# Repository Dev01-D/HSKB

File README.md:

# HSKB – Happy Sabi KeyBoard

## About the HSKB

The HSKB is a custom mechanical keyboard inspired by the minimalist layout and functionality of the HHKB (Happy Hacking Keyboard). It reflects a philosophy of simplicity, precision, and personal expression.

Designed with a true HHKB layout, the HSKB features a 6u spacebar and an integrated plate design that supports both plate-mounted and PCB-mounted stabilizers. Drawing inspiration from the legendary HHKB and driven by a passion for thoughtful design and community collaboration, this project has been a personal journey—learning new software, iterating through multiple prototypes, and spending approximately three months refining every detail.

I am excited to share the HSKB with the open-source community and hope it inspires others to create and contribute. This project would not have been possible without the support and inspiration from the keyboard community.

## Why Choose the HSKB?

Many keyboards with a similar HHKB-inspired layout are often positioned as luxury items, carrying a high price tag and limited customization options. The HSKB offers a more affordable entry point without sacrificing quality or flexibility. Its open-source nature means you can modify and adapt it to suit your preferences—whether it's changing the key mapping, adjusting the stabilizers, or customizing the case.

The HSKB provides a unique balance of cost-efficiency and personalization. It's an excellent option for enthusiasts looking to explore the HHKB layout without breaking the bank. Whether you're new to mechanical keyboards or an experienced hobbyist, the HSKB offers a rewarding, hands-on experience while remaining accessible and adaptable.

## Unity Switch & Andy's Man Club

This project is also inspired by **Matty's Unity switch**, created in support of **Andy's Man Club**, a mental health charity promoting open conversations and community support. As part of this commitment, one of the five initial HSKBs will be donated to a charity raffle to raise funds for this meaningful cause.

If you use or modify this project, please consider supporting **Andy's Man Club** or a mental health charity in your community.

- https://andysmanclub.co.uk/
- https://thoccexchange.com/

## Features

- **Minimalist Layout** – Inspired by the HHKB design
- **Custom PCB & Case Files** – Fully customizable and open-source (thanks to **TheVoid** for helping with this)
- **Community-Driven** – Built with love, feedback, and support

## What's Included

- [PCB design files (KiCad)](https://github.com/Dev01-D/HSKB/tree/main/PCB%20Files)
- [Case design files (STEP, STL for 3D printing)](https://github.com/Dev01-D/HSKB/tree/main/HSKB%20STL)
- [HS Firmware configuration (QMK/VIA-compatible)](https://github.com/Dev01-D/HSKB/tree/main/PCB%20Files/VoidHHKB-Hotswap/firmware)
- [Solder Firmware configuration (QMK/VIA-compatible)](https://github.com/Dev01-D/HSKB/tree/main/PCB%20Files/VoidHHKB-Solder/firmware)

## Getting Started

1. **Clone the repository:**
    ```bash
    git clone https://github.com/Dev01-D/hskb.git
    cd hskb
    ```

2. **Explore the design files:**
   - PCB files: Located in the `/pcb` directory
   - Case files: Located in the `/case` directory
   - Firmware: Instructions in `/firmware` for flashing QMK/VIA

3. **Manufacture & Build:**
   - Order your PCB from your preferred manufacturer
   - Print the case using the provided STL files
   - Assemble the board using the included BOM (Bill of Materials)

## Contributing

Contributions and improvements are welcome! Feel free to submit issues, pull requests, or ideas to enhance the HSKB.

1. Fork the repository
2. Create a new branch
3. Submit a pull request

## License

This project is released under the **MIT License** – you're free to use, modify, and share it. Please credit this repository if you share your own builds.

## Support

If you build your own HSKB, I would love to see it! Share your creations and thoughts.

Consider donating to **Andy's Man Club** or any mental health charity to help continue supporting important community work.

Thank you for being a part of the journey.

**Happy building!**

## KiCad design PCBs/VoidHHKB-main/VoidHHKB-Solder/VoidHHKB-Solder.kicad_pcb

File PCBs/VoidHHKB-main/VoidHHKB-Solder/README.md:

# VoidHHKB-Solder

## Ordering from JLCPCB

1) Head to the [JLCPCB order page](https://cart.jlcpcb.com/quote).

2) Upload the `VoidHHKB-Solder.zip` file in `production/`.

3) Set the quantity of the PCBs you want made.

4) Set your desired PCB parameters. Here are some suggested parameters: (Everything else can be kept at their default)

- PCB Color: **Purple**
- Surface Finish: **ENIG**
- Remove Order Number: **Yes**   

5) Enable the PCB Assembly option at the bottom, and set the following parameters:

- PCBA Type: **Standard**
- Assembly Side: **Bottom**

6) Press `Confirm` at the bottom or `NEXT` on the right to get to the next page.

7) Click `NEXT` to get to the Bill of Materials tab.

8) Click `Add BOM File` and select the `bom.csv` file in `production/`.

9) Click `Add CPL File` and select the `positions.csv` file in `production/`. Click `Process BOM & CPL` to proceed.

10) You should be presented with a list of all the components and quantities needed. Double check there are no missing components. If there are, you will have to find substitute components for it. Click `NEXT` to proceed.

11) You should be presented with a view of the PCB and its components. Click `NEXT` to proceed.

12) You should see a breakdown of the price for the PCBs you want to order. Select `Keyboard - HS Code 847330` under `Office Appliance Accessories` for the Product Description.

13) Save to cart, and pay for it!

## Flashing Firmware

1) Install and launch [QMK Toolbox](https://qmk.fm/toolbox)

2) Connect PCB via USB. Hold down reset button to enter bootloader

3) Under 'Local file' open firmware/void_voidhhkb_via.bin. Everything else can be left as default (MCU should be ATmega32U4)

4) Click Flash!

5) Unplug and plug in again to complete set up

## Using VIA

Temp instructions until I get around to merging files into QMK repo...
1) To edit keymap in via open web page and select 'Design' on the top ribbon

2) Click 'Load Draft Definition' and load '/firmware/voidhhkb/via.json'

## Build your own firmware

- Files have been included under 'firmware' if you want to build the bin files yourself.
- This is fairly trivial to do by following the [QMK Tutorial](https://docs.qmk.fm/newbs)

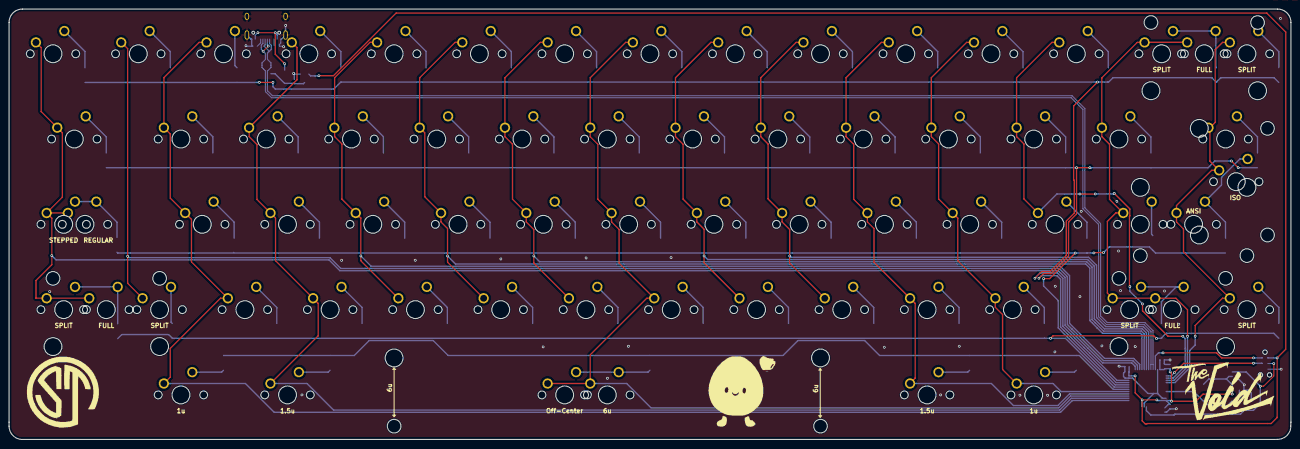
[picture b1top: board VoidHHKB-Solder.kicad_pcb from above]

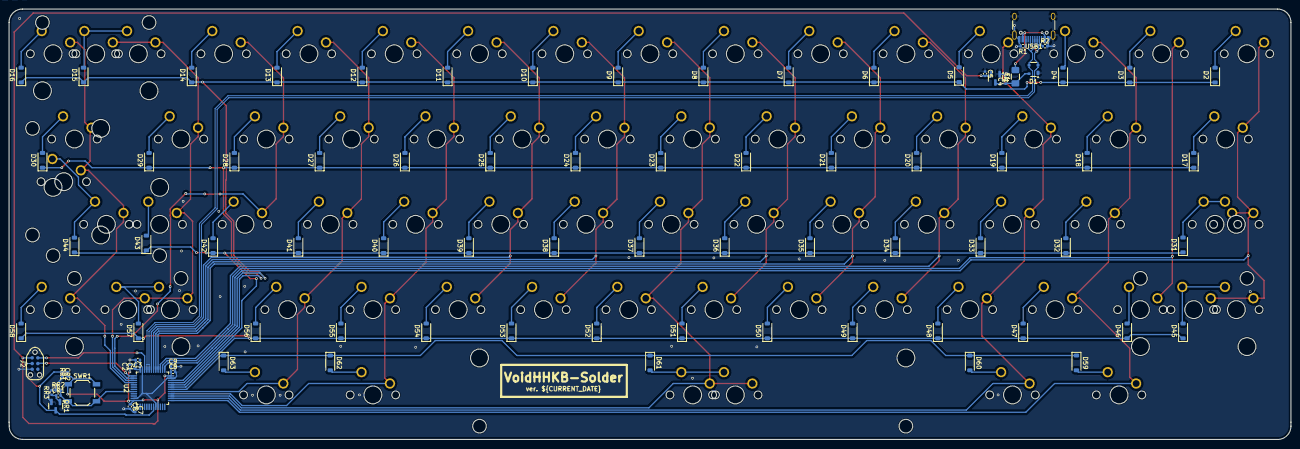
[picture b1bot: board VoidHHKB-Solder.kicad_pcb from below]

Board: 2 copper layers, 286.4 x 96.1 mm, 160 parts (86 on the bottom side), 95 nets.

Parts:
C1, C8: 4.7uF; C_0402_1005Metric
C2, C3, C7, C9: 100nF; C_0402_1005Metric
C4, C5, C6: 1uF; C_0402_1005Metric
CR1: 10uF; C_0402_1005Metric
CR2: 1uF; C_0402_1005Metric
D1: PRTR5V0U2X; SOT-143
D2, D3, D4, D5, D6, D7, D8, D9, D10, D11, D12, D13, D14, D15, D16, D17, D18, D19, D20, D21, D22, D23, D24, D25, D26, D27, D28, D29, D30, D31, D32, D33, D34, D35, D36, D37, D38, D39, D40, D41, D42, D43, D44, D45, D46, D47, D48, D49, D50, D51, D52, D53, D54, D55, D56, D57, D58, D59, D60, D61, D62, D63: 1N4148W; D_SOD-123
F1: 500mA; Fuse_1206_3216Metric_Pad1.42x1.75mm_HandSolder
J2: TC2030_SWD; CON_TC2030_outlined
MX1: Esc; SW_MX_1u
MX2: 1; SW_MX_1u
MX3: 2; SW_MX_1u
MX4: 3; SW_MX_1u
MX5: 4; SW_MX_1u
MX6: 5; SW_MX_1u
MX7: 6; SW_MX_1u
MX8: 7; SW_MX_1u
MX9: 8; SW_MX_1u
MX10: 9; SW_MX_1u
MX11: 10; SW_MX_1u
MX12: -; SW_MX_1u
MX13: =; SW_MX_1u
MX14: \; SW_MX_1u
MX15: `; SW_MX_1u
MX16: Full Backspace; SW_MX_1u
MX17: Tab; SW_MX_1.5u
MX18: Q; SW_MX_1u
MX19: W; SW_MX_1u
MX20: E; SW_MX_1u
MX21: R; SW_MX_1u
MX22: T; SW_MX_1u
MX23: Y; SW_MX_1u
MX24: U; SW_MX_1u
MX25: I; SW_MX_1u
MX26: O; SW_MX_1u
MX27: P; SW_MX_1u
MX28: [; SW_MX_1u
MX29: ]; SW_MX_1u
MX30: Backspace; SW_MX_1.5u
MX31: Stepped Caps; SW_MX_1.75u_STP_1.25
MX32: A; SW_MX_1u
MX33: S; SW_MX_1u
MX34: D; SW_MX_1u
MX35: F; SW_MX_1u
MX36: G; SW_MX_1u
MX37: H; SW_MX_1u
MX38: J; SW_MX_1u
MX39: K; SW_MX_1u
MX40: L; SW_MX_1u
MX41: ;; SW_MX_1u
MX42: '; SW_MX_1u
MX43, MX48: NUHS; SW_MX_1u
MX44: ANSI Enter; SW_MX_1u
MX45: Caps; SW_MX_1.75u
MX46: ISO Enter; SW_MX_1u
MX47: LShift; SW_MX_1u
MX49: Z; SW_MX_1u
MX50: X; SW_MX_1u
MX51: C; SW_MX_1u
MX52: V; SW_MX_1u
MX53: B; SW_MX_1u
MX54: N; SW_MX_1u
MX55: M; SW_MX_1u
MX56: ,; SW_MX_1u
MX57: .; SW_MX_1u
MX58: /; SW_MX_1u
MX59: RShift 1.75u; SW_MX_1.75u
MX60: fn; SW_MX_1u
MX61: LShift 1.25u; SW_MX_1.25u
MX62: RShift 2.75u; SW_MX_1u
MX63, MX67: Alt; SW_MX_1u
MX64, MX66: Super; SW_MX_1.5u
MX65: Spacebar; SW_MX_1u
MX68: Off Center Spacebar; SW_MX_1u
QR1: 2N7002; SOT-23
R1, R2: 5k1; R_0402_1005Metric
RR1: 33k; R_0402_1005Metric
RR2: 10k; R_0402_1005Metric
RR3: 100k; R_0402_1005Metric
S1: 2u Backspace; STAB_MX_2u
S2: 2.25u ANSI Enter; STAB_MX_2.25u
S3: ISO Enter; STAB_MX_ISO-ROT
S4: 2.25 LShift; STAB_MX_2.25u
S5: 2.75 RShift; STAB_MX_2.75u
S6: 6u Spacebar; STAB_MX_6u_New
SWR1: TS-1187A-B-A-B; SW_SPST_TL3342
U1: XC6206P332MR; SOT-23
U2: STM32F072CBT6; LQFP-48_7x7mm_P0.5mm
USB1: USB_C_Receptacle_USB2.0_16P; USB_C_Receptacle_HRO_TYPE-C-31-M-12

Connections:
+3V3: C1.1, C2.1, C3.1, C5.2, C6.1, C7.1, C8.1, C9.1, J2.1 (VCC), RR1.1, SWR1.1, U1.2 (VO), U2.9 (VDDA), U2.24 (VDD), U2.36 (VDDIO2), U2.48 (VDD)
+5V: C4.1, D1.4 (VCC), F1.1, U1.3 (VI)
/CC1: R2.1, USB1.A5 (CC1)
/CC2: R1.1, USB1.B5 (CC2)
BOOT0: CR1.2, RR2.2, SWR1.2, U2.44 (BOOT0)
D+: D1.3 (I/O2), U2.33 (PA12), USB1.A6 (D+), USB1.B6 (D+)
D-: D1.2 (I/O1), U2.32 (PA11), USB1.A7 (D-), USB1.B7 (D-)
GND: C1.2, C2.2, C3.2, C4.2, C5.1, C6.2, C7.2, C8.2, C9.2, CR2.2, D1.1 (GND), J2.5 (GND), QR1.2 (S), R1.2, R2.2, RR2.1, RR3.2, U1.1 (GND), U2.8 (VSSA), U2.23 (VSS), U2.35 (VSS), U2.47 (VSS), USB1.A1 (GND), USB1.A12 (GND), USB1.B1 (GND), USB1.B12 (GND), USB1.S1 (SHIELD)
NRST: CR2.1, J2.3 (~RST), QR1.3 (D), RR1.2, U2.7 (NRST)
unnamed: D2.2 (A), MX1.2
unnamed: D3.2 (A), MX2.2
unnamed: D4.2 (A), MX3.2
unnamed: D5.2 (A), MX4.2
unnamed: D6.2 (A), MX5.2
unnamed: D7.2 (A), MX6.2
unnamed: D8.2 (A), MX7.2
unnamed: D9.2 (A), MX8.2
unnamed: D10.2 (A), MX9.2
unnamed: D11.2 (A), MX10.2
unnamed: D12.2 (A), MX11.2
unnamed: D13.2 (A), MX12.2
unnamed: D14.2 (A), MX13.2
unnamed: D15.2 (A), MX14.2, MX16.2
unnamed: D16.2 (A), MX15.2
unnamed: D17.2 (A), MX17.2
unnamed: D18.2 (A), MX18.2
unnamed: D19.2 (A), MX19.2
unnamed: D20.2 (A), MX20.2
unnamed: D21.2 (A), MX21.2
unnamed: D22.2 (A), MX22.2
unnamed: D23.2 (A), MX23.2
unnamed: D24.2 (A), MX24.2
unnamed: D25.2 (A), MX25.2
unnamed: D26.2 (A), MX26.2
unnamed: D27.2 (A), MX27.2
unnamed: D28.2 (A), MX28.2
unnamed: D29.2 (A), MX29.2
unnamed: D30.2 (A), MX30.2
unnamed: D31.2 (A), MX31.2, MX45.2
unnamed: D32.2 (A), MX32.2
unnamed: D33.2 (A), MX33.2
unnamed: D34.2 (A), MX34.2
unnamed: D35.2 (A), MX35.2
unnamed: D36.2 (A), MX36.2
unnamed: D37.2 (A), MX37.2
unnamed: D38.2 (A), MX38.2
unnamed: D39.2 (A), MX39.2
unnamed: D40.2 (A), MX40.2
unnamed: D41.2 (A), MX41.2
unnamed: D42.2 (A), MX42.2
unnamed: D43.2 (A), MX43.2
unnamed: D44.2 (A), MX44.2, MX46.2
unnamed: D45.2 (A), MX47.2, MX61.2
unnamed: D46.2 (A), MX48.2
unnamed: D47.2 (A), MX49.2
unnamed: D48.2 (A), MX50.2
unnamed: D49.2 (A), MX51.2
unnamed: D50.2 (A), MX52.2
unnamed: D51.2 (A), MX53.2
unnamed: D52.2 (A), MX54.2
unnamed: D53.2 (A), MX55.2
unnamed: D54.2 (A), MX56.2
unnamed: D55.2 (A), MX57.2
unnamed: D56.2 (A), MX58.2
unnamed: D57.2 (A), MX59.2, MX62.2
unnamed: D58.2 (A), MX60.2
unnamed: D59.2 (A), MX63.2
unnamed: D60.2 (A), MX64.2
unnamed: D61.2 (A), MX65.2, MX68.2
unnamed: D62.2 (A), MX66.2
unnamed: D63.2 (A), MX67.2
unnamed: CR1.1, QR1.1 (G), RR3.1
PA3: MX3.1, MX18.1, MX32.1, MX49.1, MX63.1, U2.13 (PA3)
PA4: MX4.1, MX19.1, MX33.1, MX50.1, MX64.1, U2.14 (PA4)
PA5: MX8.1, MX23.1, MX37.1, MX54.1, MX65.1, MX68.1, U2.15 (PA5)
PA6: MX11.1, MX26.1, MX40.1, MX57.1, MX66.1, U2.16 (PA6)
PA7: MX12.1, MX27.1, MX41.1, MX58.1, MX67.1, U2.17 (PA7)
PA8: MX7.1, MX22.1, MX36.1, MX53.1, U2.29 (PA8)
PA9: MX9.1, MX24.1, MX38.1, MX55.1, U2.30 (PA9)
PA10: MX10.1, MX25.1, MX39.1, MX56.1, U2.31 (PA10)
PA15: MX13.1, MX28.1, MX42.1, U2.38 (PA15)
PB0: D59.1 (K), D60.1 (K), D61.1 (K), D62.1 (K), D63.1 (K), U2.18 (PB0)
PB1: D45.1 (K), D46.1 (K), D47.1 (K), D48.1 (K), D49.1 (K), D50.1 (K), D51.1 (K), D52.1 (K), D53.1 (K), D54.1 (K), D55.1 (K), D56.1 (K), D57.1 (K), D58.1 (K), U2.19 (PB1)
PB2: D31.1 (K), D32.1 (K), D33.1 (K), D34.1 (K), D35.1 (K), D36.1 (K), D37.1 (K), D38.1 (K), D39.1 (K), D40.1 (K), D41.1 (K), D42.1 (K), D43.1 (K), D44.1 (K), U2.20 (PB2)
PB3: MX14.1, MX16.1, MX29.1, MX43.1, MX59.1, MX62.1, U2.39 (PB3)
PB4: MX15.1, MX30.1, MX44.1, MX46.1, MX60.1, U2.40 (PB4)
PB10: D17.1 (K), D18.1 (K), D19.1 (K), D20.1 (K), D21.1 (K), D22.1 (K), D23.1 (K), D24.1 (K), D25.1 (K), D26.1 (K), D27.1 (K), D28.1 (K), D29.1 (K), D30.1 (K), U2.21 (PB10)
PB11: D2.1 (K), D3.1 (K), D4.1 (K), D5.1 (K), D6.1 (K), D7.1 (K), D8.1 (K), D9.1 (K), D10.1 (K), D11.1 (K), D12.1 (K), D13.1 (K), D14.1 (K), D15.1 (K), D16.1 (K), U2.22 (PB11)
PB12: MX1.1, MX17.1, MX31.1, MX45.1, MX47.1, MX61.1, U2.25 (PB12)
PB13: MX2.1, MX48.1, U2.26 (PB13)
PB14: MX5.1, MX20.1, MX34.1, MX51.1, U2.27 (PB14)
PB15: MX6.1, MX21.1, MX35.1, MX52.1, U2.28 (PB15)
SWCLK: J2.4 (SWCLK), U2.37 (PA14)
SWDIO: J2.2 (SWDIO), U2.34 (PA13)
VBUS: F1.2, USB1.A4 (VBUS), USB1.A9 (VBUS), USB1.B4 (VBUS), USB1.B9 (VBUS)

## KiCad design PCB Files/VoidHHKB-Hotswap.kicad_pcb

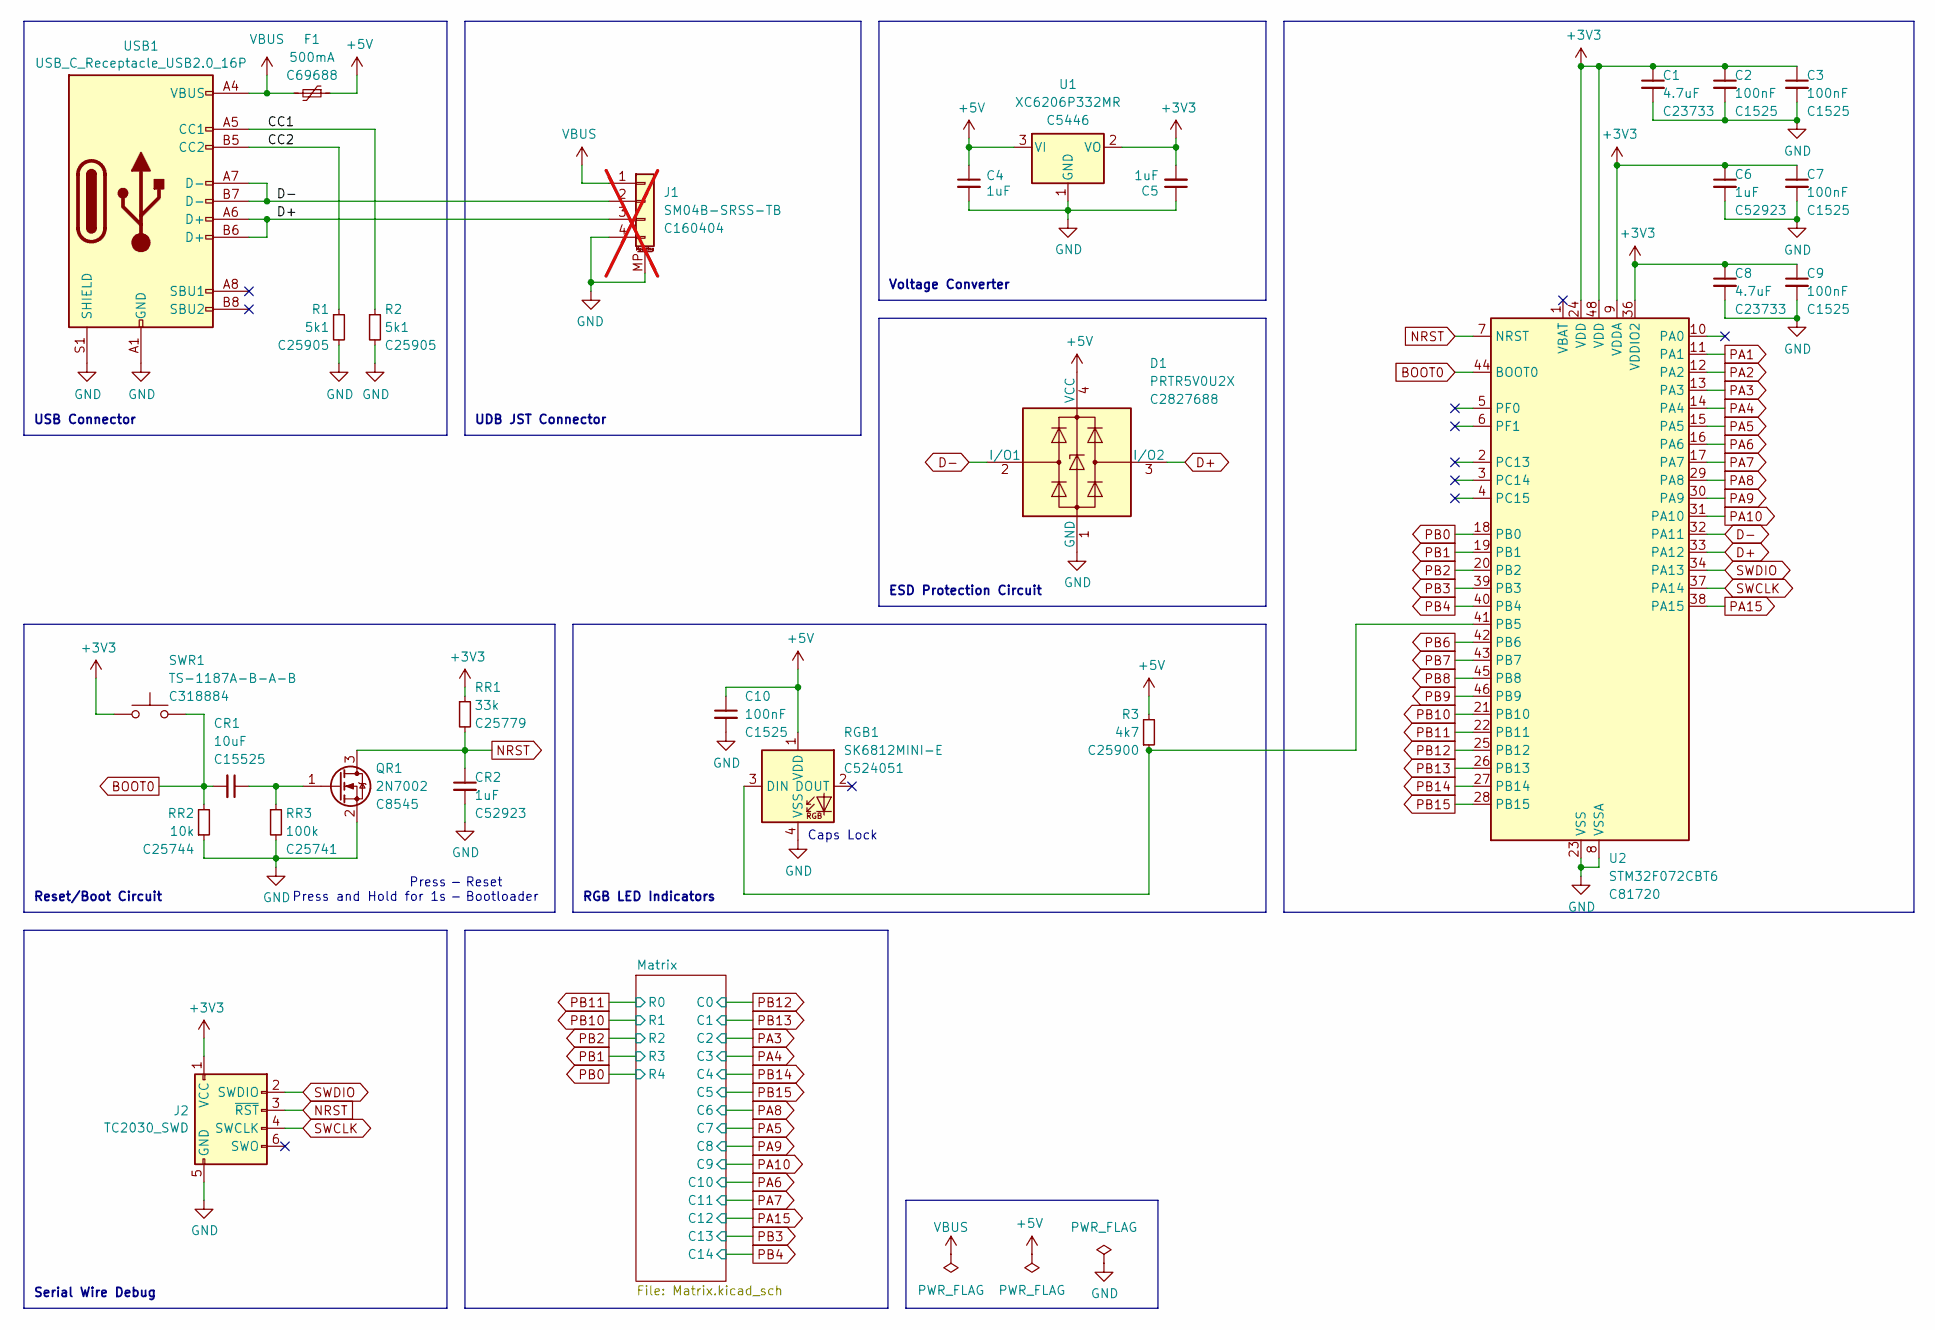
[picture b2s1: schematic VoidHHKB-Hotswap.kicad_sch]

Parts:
C1, C8: 4.7uF; C_0402_1005Metric; MPN CL05A475MP5NRNC; LCSC C23733
C2, C3, C7, C9, C10: 100nF; C_0402_1005Metric; MPN CL05B104KO5NNNC; LCSC C1525
C4, C5, C6: 1uF; C_0402_1005Metric; MPN CL05A105KA5NQNC; LCSC C52923
CR1: 10uF; C_0402_1005Metric; MPN CL05A106MQ5NUNC; LCSC C15525
CR2: 1uF; C_0402_1005Metric; MPN CL05A105KA5NQNC; LCSC C52923
D1: PRTR5V0U2X; SOT-143; MPN PRTR5V0U2X; LCSC C2827688
F1: 500mA; Fuse_1206_3216Metric_Pad1.42x1.75mm_HandSolder; MPN nSMD050; LCSC C69688
J1: SM04B-SRSS-TB; JST_SH_SM04B-SRSS-TB_1x04-1MP_P1.00mm_Horizontal; MPN SM04B-SRSS-TB(LF)(SN); LCSC C160404; not fitted
J2: TC2030_SWD; CON_TC2030_outlined
QR1: 2N7002; SOT-23; MPN 2N7002; LCSC C8545
R1, R2: 5k1; R_0402_1005Metric; MPN 0402WGF5101TCE; LCSC C25905
R3: 4k7; R_0402_1005Metric; MPN 0402WGF4701TCE; LCSC C25900
RGB1: SK6812MINI-E; LED_6028R; MPN SK6812MINI-E; LCSC C524051
RR1: 33k; R_0402_1005Metric; MPN 0402WGF3302TCE; LCSC C25779
RR2: 10k; R_0402_1005Metric; MPN 0402WGF1002TCE; LCSC C25744
RR3: 100k; R_0402_1005Metric; MPN 0402WGF1003TCE; LCSC C25741
SWR1: TS-1187A-B-A-B; SW_SPST_TL3342; MPN TS-1187A-B-A-B; LCSC C318884
U1: XC6206P332MR; SOT-23; MPN XC6206P332MR-G; LCSC C5446
U2: STM32F072CBT6; LQFP-48_7x7mm_P0.5mm; MPN STM32F072CBT6; LCSC C81720
USB1: USB_C_Receptacle_USB2.0_16P; USB_C_Receptacle_HRO_TYPE-C-31-M-12; MPN TYPE-C-31-M-12; LCSC C165948

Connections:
+3V3: C1.1, C2.1, C3.1, C5.2, C6.1, C7.1, C8.1, C9.1, J2.1 (VCC), RR1.1, SWR1.1, U1.2 (VO), U2.9 (VDDA), U2.24 (VDD), U2.36 (VDDIO2), U2.48 (VDD)
+5V: C4.1, C10.1, D1.4 (VCC), F1.1, R3.2, RGB1.1 (VDD), U1.3 (VI)
/CC1: R2.1, USB1.A5 (CC1)
/CC2: R1.1, USB1.B5 (CC2)
BOOT0: CR1.2, RR2.2, SWR1.2, U2.44 (BOOT0)
D+: D1.3 (I/O2), J1.3, U2.33 (PA12), USB1.A6 (D+), USB1.B6 (D+)
D-: D1.2 (I/O1), J1.2, U2.32 (PA11), USB1.A7 (D-), USB1.B7 (D-)
GND: C1.2, C2.2, C3.2, C4.2, C5.1, C6.2, C7.2, C8.2, C9.2, C10.2, CR2.2, D1.1 (GND), J1.4, J1.MP (MountPin), J2.5 (GND), QR1.2 (S), R1.2, R2.2, RGB1.4 (VSS), RR2.1, RR3.2, U1.1 (GND), U2.8 (VSSA), U2.23 (VSS), U2.35 (VSS), U2.47 (VSS), USB1.A1 (GND), USB1.A12 (GND), USB1.B1 (GND), USB1.B12 (GND), USB1.S1 (SHIELD)
NRST: CR2.1, J2.3 (~RST), QR1.3 (D), RR1.2, U2.7 (NRST)
unnamed: CR1.1, QR1.1 (G), RR3.1
unnamed: R3.1, RGB1.3 (DIN), U2.41 (PB5)
PA1: U2.11 (PA1)
PA2: U2.12 (PA2)
PA3: U2.13 (PA3); also elsewhere on the board
PA4: U2.14 (PA4); also elsewhere on the board
PA5: U2.15 (PA5); also elsewhere on the board
PA6: U2.16 (PA6); also elsewhere on the board
PA7: U2.17 (PA7); also elsewhere on the board
PA8: U2.29 (PA8); also elsewhere on the board
PA9: U2.30 (PA9); also elsewhere on the board
PA10: U2.31 (PA10); also elsewhere on the board
PA15: U2.38 (PA15); also elsewhere on the board
PB0: U2.18 (PB0); also elsewhere on the board
PB1: U2.19 (PB1); also elsewhere on the board
PB2: U2.20 (PB2); also elsewhere on the board
PB3: U2.39 (PB3); also elsewhere on the board
PB4: U2.40 (PB4); also elsewhere on the board
PB6: U2.42 (PB6)
PB7: U2.43 (PB7)
PB8: U2.45 (PB8)
PB9: U2.46 (PB9)
PB10: U2.21 (PB10); also elsewhere on the board
PB11: U2.22 (PB11); also elsewhere on the board
PB12: U2.25 (PB12); also elsewhere on the board
PB13: U2.26 (PB13); also elsewhere on the board
PB14: U2.27 (PB14); also elsewhere on the board
PB15: U2.28 (PB15); also elsewhere on the board
SWCLK: J2.4 (SWCLK), U2.37 (PA14)
SWDIO: J2.2 (SWDIO), U2.34 (PA13)
VBUS: F1.2, J1.1, USB1.A4 (VBUS), USB1.A9 (VBUS), USB1.B4 (VBUS), USB1.B9 (VBUS)

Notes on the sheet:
Reset Bootloader
- -
ESD Protection Circuit
Voltage Converter
Caps Lock
Serial Wire Debug
Press Press and Hold for 1s
Reset/Boot Circuit
USB Connector
UDB JST Connector
RGB LED Indicators

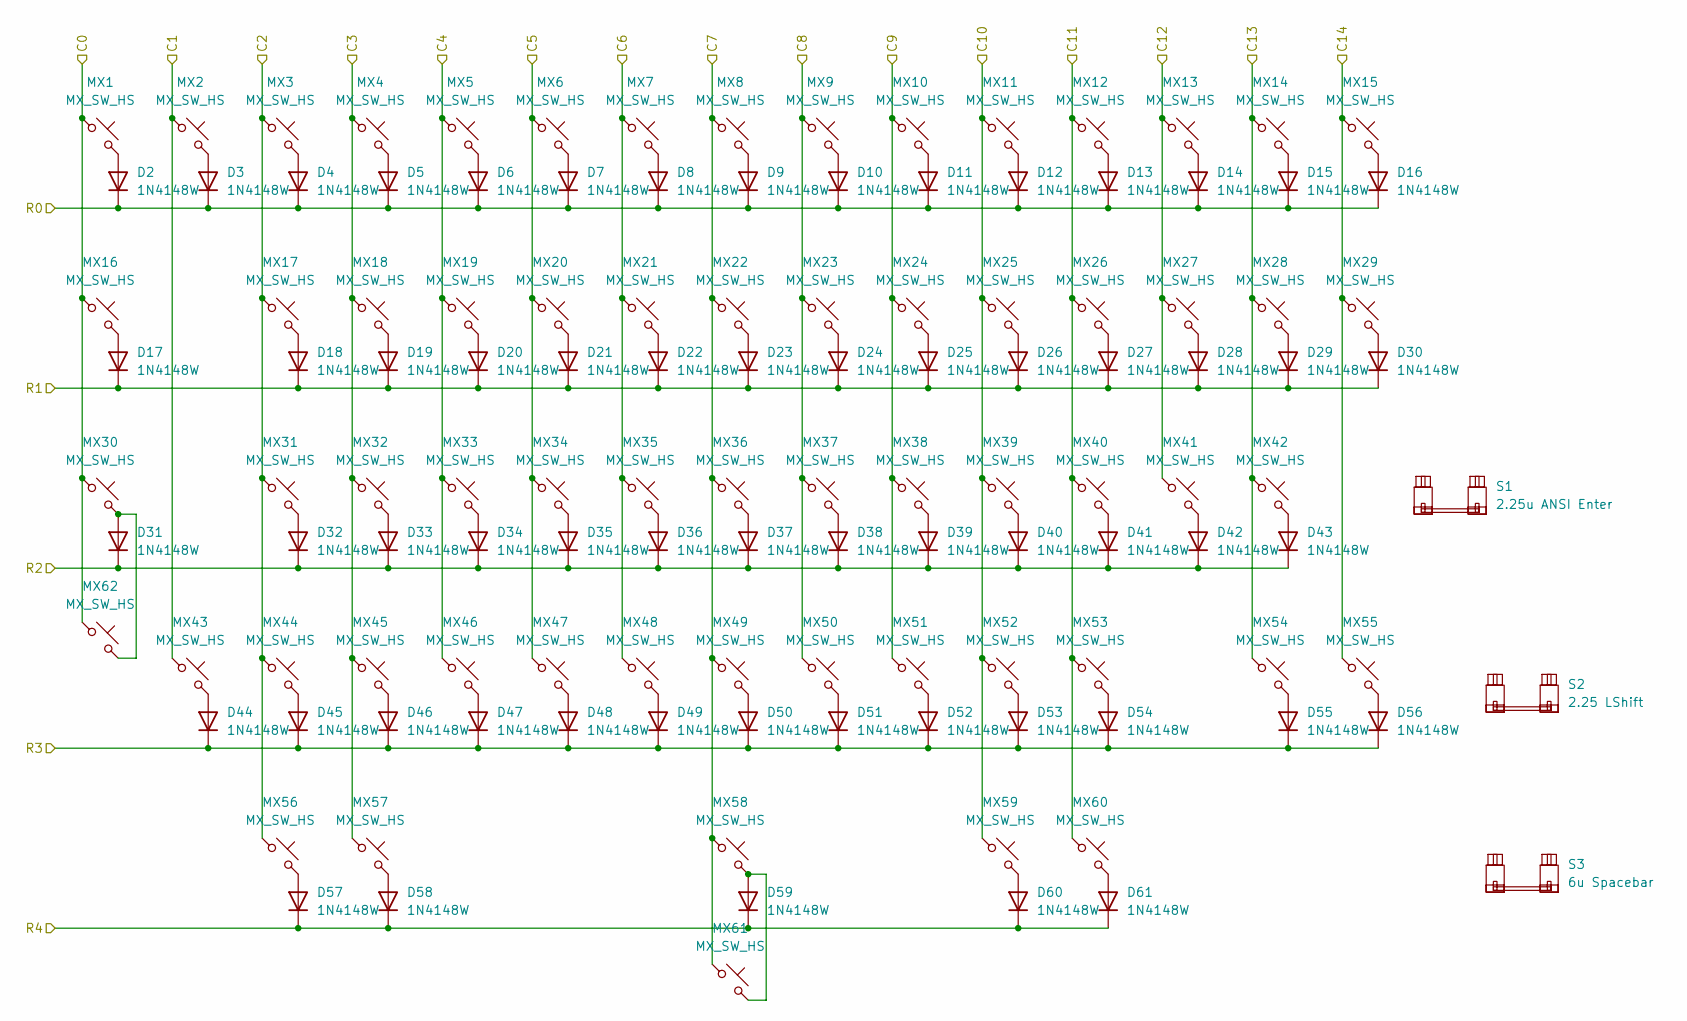
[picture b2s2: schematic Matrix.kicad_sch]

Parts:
D2, D3, D4, D5, D6, D7, D8, D9, D10, D11, D12, D13, D14, D15, D16, D17, D18, D19, D20, D21, D22, D23, D24, D25, D26, D27, D28, D29, D30, D31, D32, D33, D34, D35, D36, D37, D38, D39, D40, D41, D42, D43, D44, D45, D46, D47, D48, D49, D50, D51, D52, D53, D54, D55, D56, D57, D58, D59, D60, D61: 1N4148W; D_SOD-123
MX1, MX2, MX3, MX4, MX5, MX6, MX7, MX8, MX9, MX10, MX11, MX12, MX13, MX14, MX15, MX17, MX18, MX19, MX20, MX21, MX22, MX23, MX24, MX25, MX26, MX27, MX28, MX31, MX32, MX33, MX34, MX35, MX36, MX37, MX38, MX39, MX40, MX41, MX42, MX43, MX44, MX45, MX46, MX47, MX48, MX49, MX50, MX51, MX52, MX53, MX55, MX56, MX58, MX60, MX61: MX_SW_HS; SW_MX_HS_CPG151101S11_1u
MX16, MX29, MX57, MX59: MX_SW_HS; SW_MX_HS_CPG151101S11_1.5u
MX30, MX54: MX_SW_HS; SW_MX_HS_CPG151101S11_1.75u
MX62: MX_SW_HS; SW_MX_HS_CPG151101S11_1.75u_STP_1.25
S1: 2.25u ANSI Enter; STAB_MX_2.25u
S2: 2.25 LShift; STAB_MX_2.25u
S3: 6u Spacebar; STAB_MX_6u_New

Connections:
unnamed: D2.2 (A), MX1.2
unnamed: D3.2 (A), MX2.2
unnamed: D4.2 (A), MX3.2
unnamed: D5.2 (A), MX4.2
unnamed: D6.2 (A), MX5.2
unnamed: D7.2 (A), MX6.2
unnamed: D8.2 (A), MX7.2
unnamed: D9.2 (A), MX8.2
unnamed: D10.2 (A), MX9.2
unnamed: D11.2 (A), MX10.2
unnamed: D12.2 (A), MX11.2
unnamed: D13.2 (A), MX12.2
unnamed: D14.2 (A), MX13.2
unnamed: D15.2 (A), MX14.2
unnamed: D16.2 (A), MX15.2
unnamed: D17.2 (A), MX16.2
unnamed: D18.2 (A), MX17.2
unnamed: D19.2 (A), MX18.2
unnamed: D20.2 (A), MX19.2
unnamed: D21.2 (A), MX20.2
unnamed: D22.2 (A), MX21.2
unnamed: D23.2 (A), MX22.2
unnamed: D24.2 (A), MX23.2
unnamed: D25.2 (A), MX24.2
unnamed: D26.2 (A), MX25.2
unnamed: D27.2 (A), MX26.2
unnamed: D28.2 (A), MX27.2
unnamed: D29.2 (A), MX28.2
unnamed: D30.2 (A), MX29.2
unnamed: D31.2 (A), MX30.2, MX62.2
unnamed: D32.2 (A), MX31.2
unnamed: D33.2 (A), MX32.2
unnamed: D34.2 (A), MX33.2
unnamed: D35.2 (A), MX34.2
unnamed: D36.2 (A), MX35.2
unnamed: D37.2 (A), MX36.2
unnamed: D38.2 (A), MX37.2
unnamed: D39.2 (A), MX38.2
unnamed: D40.2 (A), MX39.2
unnamed: D41.2 (A), MX40.2
unnamed: D42.2 (A), MX41.2
unnamed: D43.2 (A), MX42.2
unnamed: D44.2 (A), MX43.2
unnamed: D45.2 (A), MX44.2
unnamed: D46.2 (A), MX45.2
unnamed: D47.2 (A), MX46.2
unnamed: D48.2 (A), MX47.2
unnamed: D49.2 (A), MX48.2
unnamed: D50.2 (A), MX49.2
unnamed: D51.2 (A), MX50.2
unnamed: D52.2 (A), MX51.2
unnamed: D53.2 (A), MX52.2
unnamed: D54.2 (A), MX53.2
unnamed: D55.2 (A), MX54.2
unnamed: D56.2 (A), MX55.2
unnamed: D57.2 (A), MX56.2
unnamed: D58.2 (A), MX57.2
unnamed: D59.2 (A), MX58.2, MX61.2
unnamed: D60.2 (A), MX59.2
unnamed: D61.2 (A), MX60.2
PA3: MX3.1, MX17.1, MX31.1, MX44.1, MX56.1; also elsewhere on the board
PA4: MX4.1, MX18.1, MX32.1, MX45.1, MX57.1; also elsewhere on the board
PA5: MX8.1, MX22.1, MX36.1, MX49.1, MX58.1, MX61.1; also elsewhere on the board
PA6: MX11.1, MX25.1, MX39.1, MX52.1, MX59.1; also elsewhere on the board
PA7: MX12.1, MX26.1, MX40.1, MX53.1, MX60.1; also elsewhere on the board
PA8: MX7.1, MX21.1, MX35.1, MX48.1; also elsewhere on the board
PA9: MX9.1, MX23.1, MX37.1, MX50.1; also elsewhere on the board
PA10: MX10.1, MX24.1, MX38.1, MX51.1; also elsewhere on the board
PA15: MX13.1, MX27.1, MX41.1; also elsewhere on the board
PB0: D57.1 (K), D58.1 (K), D59.1 (K), D60.1 (K), D61.1 (K); also elsewhere on the board
PB1: D44.1 (K), D45.1 (K), D46.1 (K), D47.1 (K), D48.1 (K), D49.1 (K), D50.1 (K), D51.1 (K), D52.1 (K), D53.1 (K), D54.1 (K), D55.1 (K), D56.1 (K); also elsewhere on the board
PB2: D31.1 (K), D32.1 (K), D33.1 (K), D34.1 (K), D35.1 (K), D36.1 (K), D37.1 (K), D38.1 (K), D39.1 (K), D40.1 (K), D41.1 (K), D42.1 (K), D43.1 (K); also elsewhere on the board
PB3: MX14.1, MX28.1, MX42.1, MX54.1; also elsewhere on the board
PB4: MX15.1, MX29.1, MX55.1; also elsewhere on the board
PB10: D17.1 (K), D18.1 (K), D19.1 (K), D20.1 (K), D21.1 (K), D22.1 (K), D23.1 (K), D24.1 (K), D25.1 (K), D26.1 (K), D27.1 (K), D28.1 (K), D29.1 (K), D30.1 (K); also elsewhere on the board
PB11: D2.1 (K), D3.1 (K), D4.1 (K), D5.1 (K), D6.1 (K), D7.1 (K), D8.1 (K), D9.1 (K), D10.1 (K), D11.1 (K), D12.1 (K), D13.1 (K), D14.1 (K), D15.1 (K), D16.1 (K); also elsewhere on the board
PB12: MX1.1, MX16.1, MX30.1, MX62.1; also elsewhere on the board
PB13: MX2.1, MX43.1; also elsewhere on the board
PB14: MX5.1, MX19.1, MX33.1, MX46.1; also elsewhere on the board
PB15: MX6.1, MX20.1, MX34.1, MX47.1; also elsewhere on the board

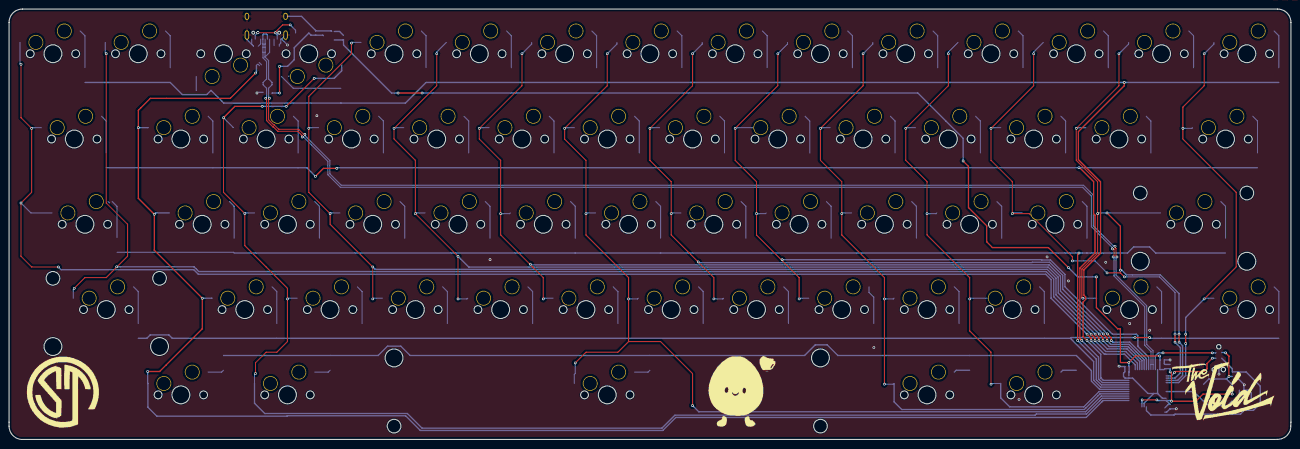
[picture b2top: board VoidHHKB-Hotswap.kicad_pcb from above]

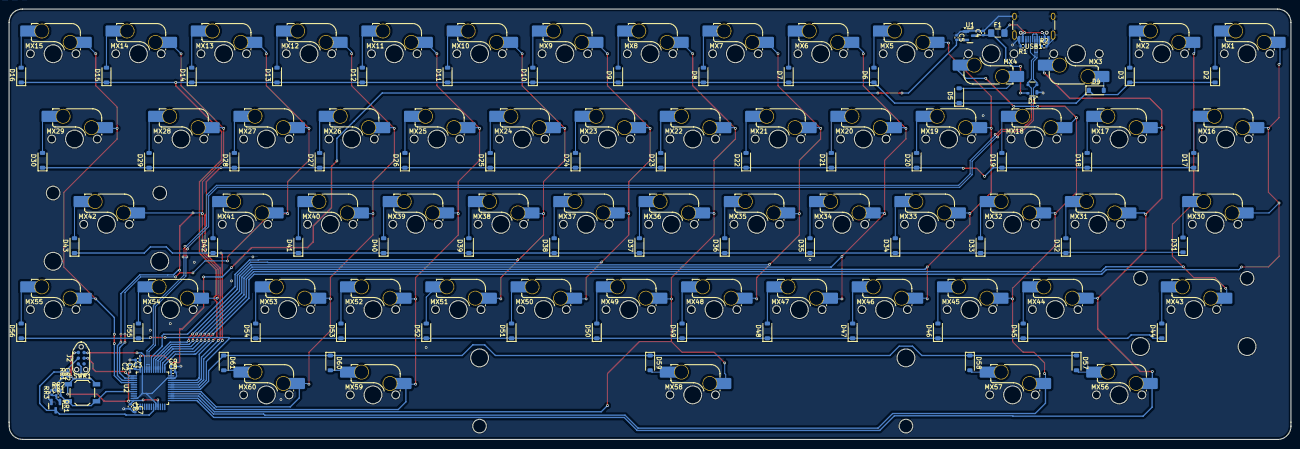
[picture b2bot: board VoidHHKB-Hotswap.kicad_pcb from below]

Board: 2 copper layers, 286.4 x 96.1 mm, 147 parts (144 on the bottom side), 93 nets.

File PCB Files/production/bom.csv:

Designator,Footprint,Quantity,Value,LCSC Part #
"C1, C8",0402,2,4.7uF,C23733
"C2, C3, C7, C9",0402,4,100nF,C1525
"C4, C5, C6, CR2",0402,4,1uF,C52923
CR1,0402,1,10uF,C15525
D1,SOT-143,1,PRTR5V0U2X,C2827688
"D10, D11, D12, D13, D14, D15, D16, D17, D18, D19, D2, D20, D21, D22, D23, D24, D25, D26, D27, D28, D29, D3, D30, D31, D32, D33, D34, D35, D36, D37, D38, D39, D4, D40, D41, D42, D43, D44, D45, D46, D47, D48, D49, D5, D50, D51, D52, D53, D54, D55, D56, D57, D58, D59, D6, D60, D61, D7, D8, D9",D_SOD-123,60,1N4148W,
F1,1206,1,500mA,C69688
"MX1, MX10, MX11, MX12, MX13, MX14, MX15, MX17, MX18, MX19, MX2, MX20, MX21, MX22, MX23, MX24, MX25, MX26, MX27, MX28, MX3, MX31, MX32, MX33, MX34, MX35, MX36, MX37, MX38, MX39, MX4, MX40, MX41, MX42, MX43, MX44, MX45, MX46, MX47, MX48, MX49, MX5, MX50, MX51, MX52, MX53, MX55, MX56, MX58, MX6, MX60, MX61, MX7, MX8, MX9",SW_MX_HS_CPG151101S11_1u,55,MX_SW_HS,
"MX16, MX29, MX57, MX59",SW_MX_HS_CPG151101S11_1.5u,4,MX_SW_HS,
"MX30, MX54",SW_MX_HS_CPG151101S11_1.75u,2,MX_SW_HS,
MX62,SW_MX_HS_CPG151101S11_1.75u_STP_1.25,1,MX_SW_HS,
QR1,SOT-23,1,2N7002,C8545
"R1, R2",0402,2,5k1,C25905
RR1,0402,1,33k,C25779
RR2,0402,1,10k,C25744
RR3,0402,1,100k,C25741
S1,STAB_MX_2.25u,1,2.25u ANSI Enter,
S2,STAB_MX_2.25u,1,2.25 LShift,
S3,STAB_MX_6u_New,1,6u Spacebar,
SWR1,SW_SPST_TL3342,1,TS-1187A-B-A-B,C318884
U1,SOT-23,1,XC6206P332MR,C5446
U2,LQFP-48_7x7mm_P0.5mm,1,STM32F072CBT6,C81720
USB1,USB_C_Receptacle_HRO_TYPE-C-31-M-12,1,USB_C_Receptacle_USB2.0_16P,C165948
